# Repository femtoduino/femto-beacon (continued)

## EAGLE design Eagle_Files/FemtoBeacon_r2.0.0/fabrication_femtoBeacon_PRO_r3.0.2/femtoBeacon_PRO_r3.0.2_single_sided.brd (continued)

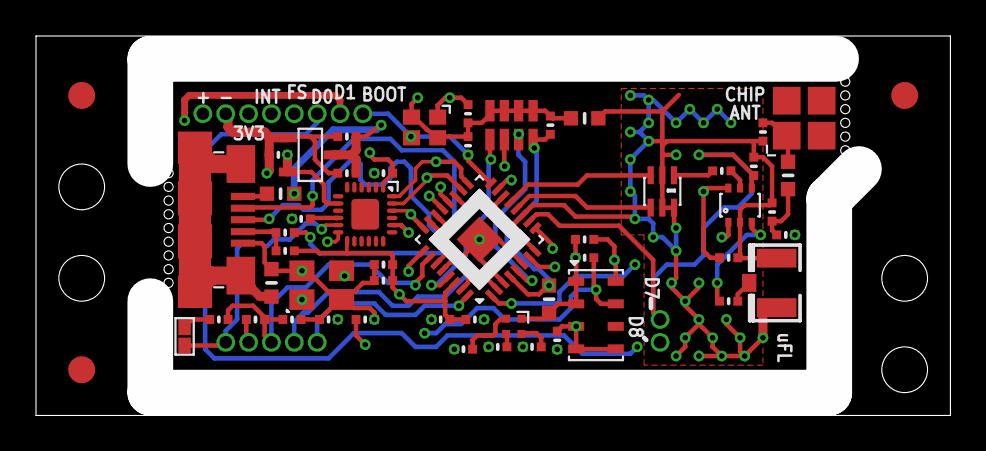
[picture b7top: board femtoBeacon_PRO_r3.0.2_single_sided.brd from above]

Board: 4 copper layers, 50.8 x 21.1 mm, 58 parts (1 on the bottom side), 43 nets.

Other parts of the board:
FID1, FID2, FID3: FIDUCIAL_1MM

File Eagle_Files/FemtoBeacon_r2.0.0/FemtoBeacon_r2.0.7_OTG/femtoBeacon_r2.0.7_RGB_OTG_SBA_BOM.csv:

##########################################################################
       Name: Placement Bill of Materials Generator

    Version: 4 (2-sided, top)
         By: Small Batch Assembly
        URL: www.smallbatchassembly.com
 SourceFile: femtoBeacon_r2.0.7_RGB_OTG.brd
   DateTime: 11/24/17 7:52 PM
      Units: inches
##########################################################################
REF,PACKAGE,VALUE,X,Y,ROTATION,
ANT_SMD   , 0479480001            , 0479480001     , 0.2137, 0.5543, 180.0
BALUN   , 0805_BALUN            , JOHANSON_2450BM15A0015E     , 0.3937, 0.5770, 270.0
BTN   , SPST_SMD            , DNP     , 0.8398, 0.3440, 270.0
C1   , PART            , 0.1uF     , 0.7968, 0.3190, 270.0
C2   , PART            , 0.1uF     , 0.6077, 0.4490, 0.0
C5   , _0402MP            , 2.2uF     , 0.7167, 0.3200, 180.0
C6   , _0402MP            , 2.2uF     , 0.5987, 0.3510, 180.0
C7   , PART            , 0.47uF     , 0.6047, 0.2910, 180.0
C8   , PART            , 0.1uF     , 0.7687, 0.7430, 180.0
C9   , PART            , 0.1uF     , 0.7318, 0.6870, 0.0
C10   , PART            , 0.1uF     , 0.5397, 0.3240, 180.0
C11   , _0402MP            , 1.2pF     , 0.3850, 0.4650, 0.0
C12   , PART            , 22pF     , 0.3937, 0.6550, 180.0
C13   , PART            , DNP     , 0.3900, 0.4350, 0.0
C14   , PART            , 9pF     , 0.5277, 0.7920, 270.0
C15   , PART            , 9pF     , 0.7167, 0.7550, 270.0
C16   , PART            , 0.1uF     , 0.6067, 0.3975, 0.0
C17   , PART            , 0.1uF     , 0.7587, 0.7160, 180.0
C21   , _0402MP            , 10uF     , 0.4267, 0.7890, 180.0
C22   , _0402MP            , 10uF     , 0.4667, 0.7560, 0.0
C31   , PART            , 10nF     , 0.5357, 0.2940, 0.0
FB1   , _0603MP            , Ferrite     , 0.7347, 0.3970, 180.0
FID1   , FIDUCIAL_1MM            , FIDUCIAL     , 0.1000, 0.3000, 0.0
FID2   , FIDUCIAL_1MM            , FIDUCIAL     , 0.1000, 0.8000, 0.0
FID3   , FIDUCIAL_1MM            , FIDUCIAL     , 1.2000, 0.8000, 0.0
IC   , QFN32            , ATSAMR21E18A-MUT     , 0.5861, 0.5907, 270.0
L1   , _0603MP            , 1.8nH     , 0.3300, 0.4650, 270.0
L6   , _0603MP            , 10uH     , 0.4317, 0.7190, 0.0
LDO_VREG   , MCP1700T-3302E/TT            , MCP1700T-3302E/TT     , 0.6581, 0.3211, 90.0
R1   , PART            , 330     , 0.7767, 0.3600, 180.0
R2   , PART            , 10K     , 0.7637, 0.3190, 270.0
R4   , PART            , 330     , 0.7760, 0.7880, 0.0
R5   , PART            , 330     , 0.7350, 0.5600, 0.0
R6   , PART            , 330     , 0.7700, 0.8150, 0.0
R7   , PART            , 330     , 0.7800, 0.8450, 0.0
R10   , PART            , 100K     , 0.7750, 0.6140, 90.0
RGBLED   , LRTB_R48G            , LRTB_R48G     , 0.8300, 0.7950, 270.0
USB   , USB_MICROB_PACKAGE            , USB_MICROB     , 0.8764, 0.5550, 90.0
XOSCRF   , TSX-3225            , 16MHz     , 0.6240, 0.7825, 0.0
